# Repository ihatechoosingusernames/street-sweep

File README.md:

# street-sweep
A low cost version of the Ferris Sweep ergonomic keyboard.

Based on a [CH552G](https://raw.githubusercontent.com/WeActStudio/WeActStudio.CH552CoreBoard/master/Datasheet/CH552DS1_en.PDF) chip, this PCB can be completely constructed with all components apart from MX switches by JLCPCB for a total of €27.28 (5x PCBs), making for a per-keyboard cost of €10.91.

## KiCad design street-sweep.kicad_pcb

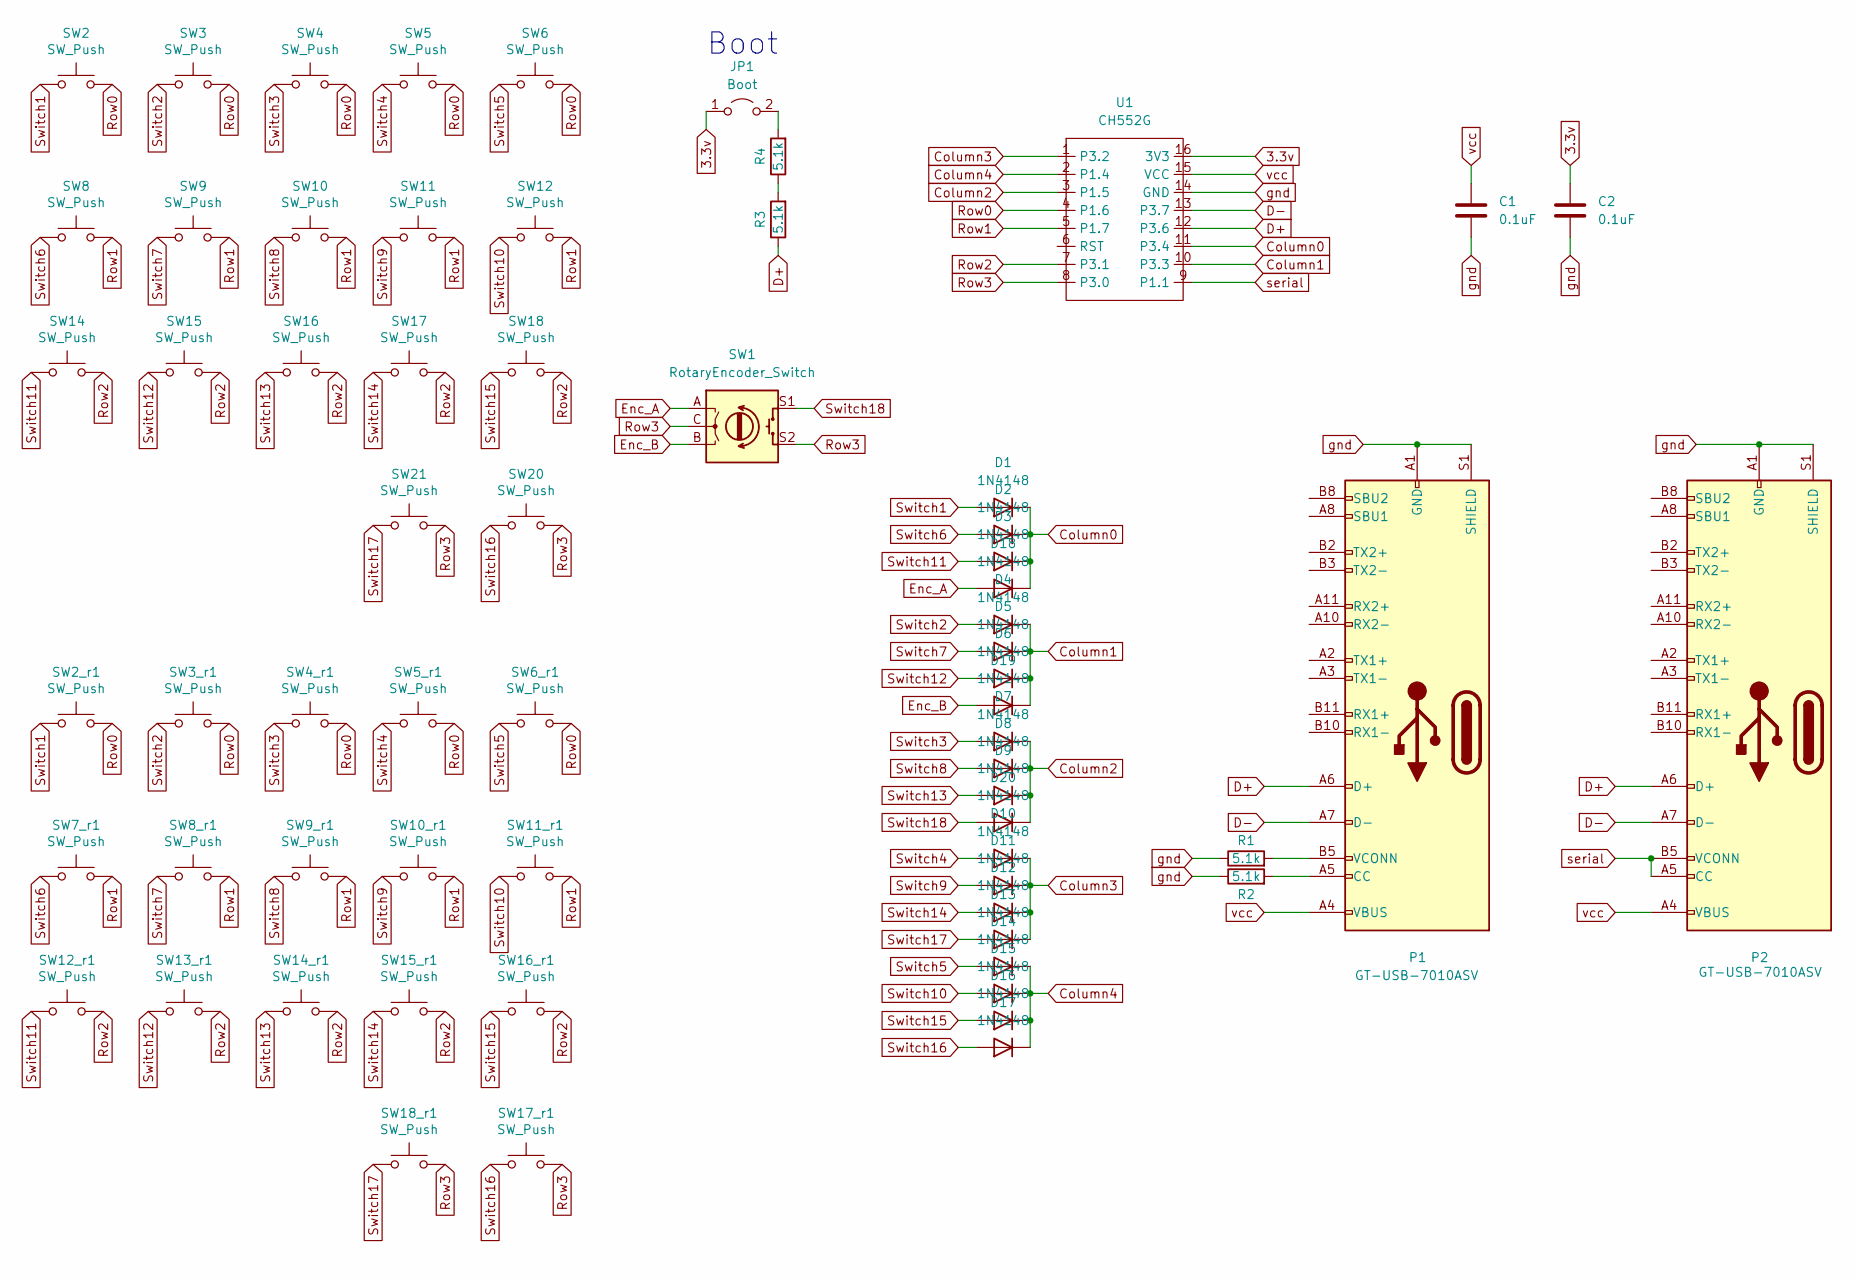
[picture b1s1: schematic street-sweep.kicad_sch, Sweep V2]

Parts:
C1, C2: 0.1uF; C_0805_2012Metric_Pad1.18x1.45mm_HandSolder
D1, D2, D3, D4, D5, D6, D7, D8, D9, D10, D11, D12, D13, D14, D15, D16, D17, D18, D19, D20: 1N4148; D_SOD-123
JP1: Boot; PinHeader_1x02_P2.54mm_Vertical
P1, P2: GT-USB-7010ASV; USB_C_Receptacle_G-Switch_GT-USB-7010ASV
R1, R2, R3, R4: 5.1k; R_0805_2012Metric
SW1: RotaryEncoder_Switch; RotaryEncoder_Alps_EC11E-Switch_Vertical_H20mm
SW2, SW2_r1, SW3, SW3_r1, SW4, SW4_r1, SW5, SW5_r1, SW6, SW6_r1, SW7_r1, SW8, SW8_r1, SW9, SW9_r1, SW10, SW10_r1, SW11, SW11_r1, SW12, SW12_r1, SW13_r1, SW14, SW14_r1, SW15, SW15_r1, SW16, SW16_r1, SW17, SW17_r1, SW18, SW18_r1, SW20, SW21: SW_Push; SW_Cherry_MX_1.00u_PCB
U1: CH552G

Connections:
3.3v: C2.1, JP1.1 (A), U1.16 (3V3)
Column0: D1.1 (K), D2.1 (K), D3.1 (K), D18.1 (K), U1.11 (P3.4)
Column1: D4.1 (K), D5.1 (K), D6.1 (K), D19.1 (K), U1.10 (P3.3)
Column2: D7.1 (K), D8.1 (K), D9.1 (K), D20.1 (K), U1.3 (P1.5)
Column3: D10.1 (K), D11.1 (K), D12.1 (K), D13.1 (K), U1.1 (P3.2)
Column4: D14.1 (K), D15.1 (K), D16.1 (K), D17.1 (K), U1.2 (P1.4)
D+: P1.A6 (D+), P2.A6 (D+), R3.1, U1.12 (P3.6)
D-: P1.A7 (D-), P2.A7 (D-), U1.13 (P3.7)
Enc_A: D18.2 (A), SW1.A
Enc_B: D19.2 (A), SW1.B
unnamed: JP1.2 (B), R4.2
unnamed: P1.A5 (CC), R2.2
unnamed: P1.B5 (VCONN), R1.2
unnamed: R3.2, R4.1
Row0: SW2.2, SW2_r1.2, SW3.2, SW3_r1.2, SW4.2, SW4_r1.2, SW5.2, SW5_r1.2, SW6.2, SW6_r1.2, U1.4 (P1.6)
Row1: SW7_r1.2, SW8.2, SW8_r1.2, SW9.2, SW9_r1.2, SW10.2, SW10_r1.2, SW11.2, SW11_r1.2, SW12.2, U1.5 (P1.7)
Row2: SW12_r1.2, SW13_r1.2, SW14.2, SW14_r1.2, SW15.2, SW15_r1.2, SW16.2, SW16_r1.2, SW17.2, SW18.2, U1.7 (P3.1)
Row3: SW1.C, SW1.S2, SW17_r1.2, SW18_r1.2, SW20.2, SW21.2, U1.8 (P3.0)
Switch1: D1.2 (A), SW2.1, SW2_r1.1
Switch2: D4.2 (A), SW3.1, SW3_r1.1
Switch3: D7.2 (A), SW4.1, SW4_r1.1
Switch4: D10.2 (A), SW5.1, SW5_r1.1
Switch5: D14.2 (A), SW6.1, SW6_r1.1
Switch6: D2.2 (A), SW7_r1.1, SW8.1
Switch7: D5.2 (A), SW8_r1.1, SW9.1
Switch8: D8.2 (A), SW9_r1.1, SW10.1
Switch9: D11.2 (A), SW10_r1.1, SW11.1
Switch10: D15.2 (A), SW11_r1.1, SW12.1
Switch11: D3.2 (A), SW12_r1.1, SW14.1
Switch12: D6.2 (A), SW13_r1.1, SW15.1
Switch13: D9.2 (A), SW14_r1.1, SW16.1
Switch14: D12.2 (A), SW15_r1.1, SW17.1
Switch15: D16.2 (A), SW16_r1.1, SW18.1
Switch16: D17.2 (A), SW17_r1.1, SW20.1
Switch17: D13.2 (A), SW18_r1.1, SW21.1
Switch18: D20.2 (A), SW1.S1
gnd: C1.2, C2.2, P1.A1 (GND), P1.A12 (GND), P1.B1 (GND), P1.B12 (GND), P1.S1 (SHIELD), P2.A1 (GND), P2.A12 (GND), P2.B1 (GND), P2.B12 (GND), P2.S1 (SHIELD), R1.1, R2.1, U1.14 (GND)
serial: P2.A5 (CC), P2.B5 (VCONN), U1.9 (P1.1)
vcc: C1.1, P1.A4 (VBUS), P1.A9 (VBUS), P1.B4 (VBUS), P1.B9 (VBUS), P2.A4 (VBUS), P2.A9 (VBUS), P2.B4 (VBUS), P2.B9 (VBUS), U1.15 (VCC)

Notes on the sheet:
Boot

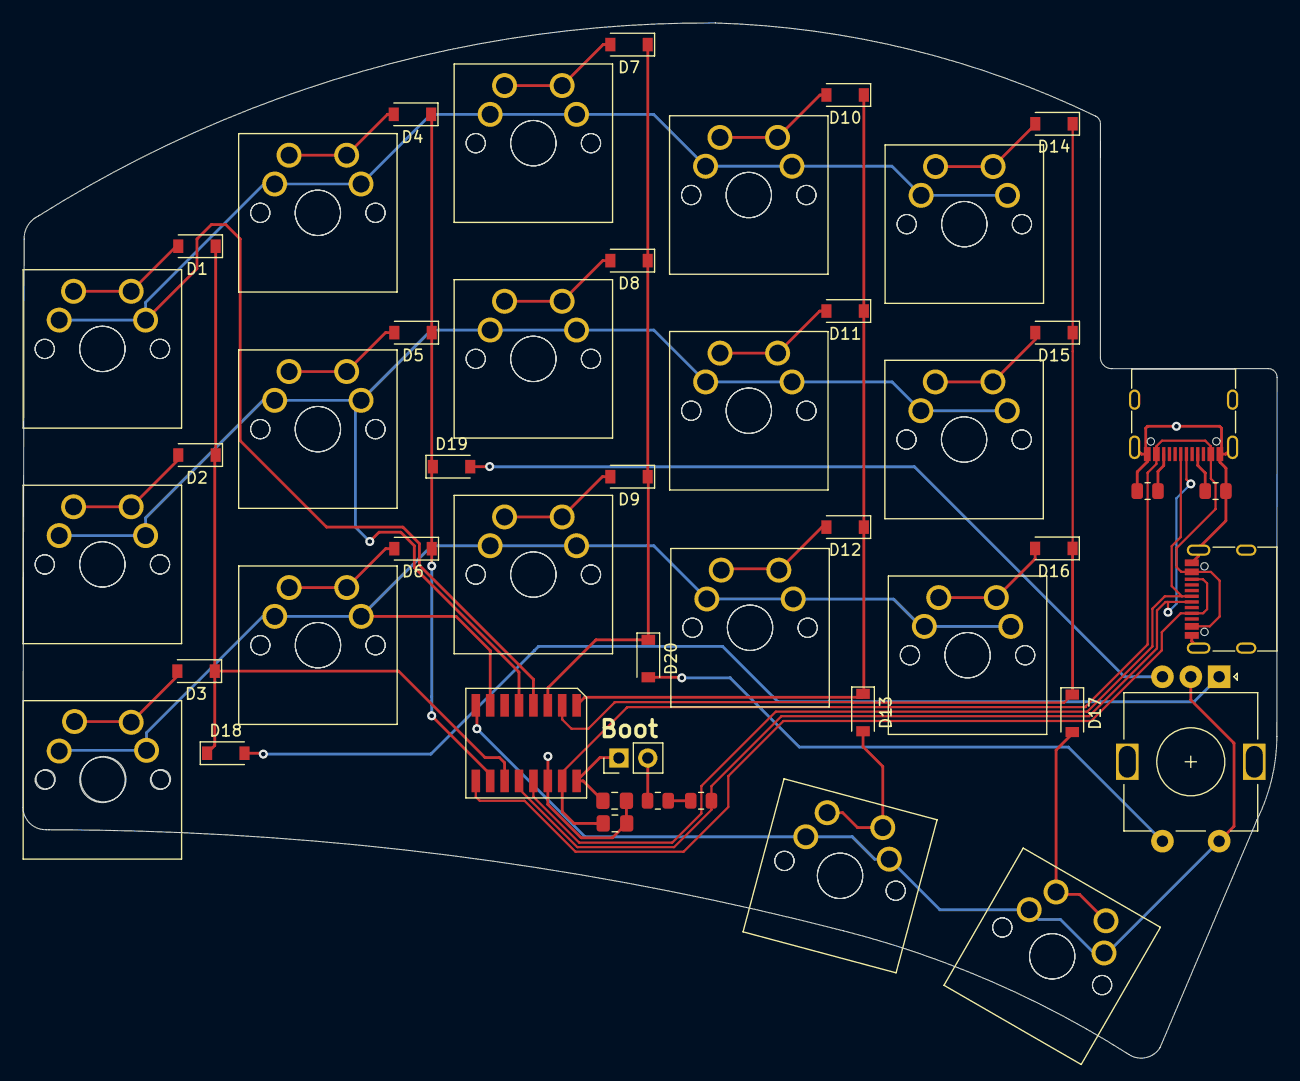
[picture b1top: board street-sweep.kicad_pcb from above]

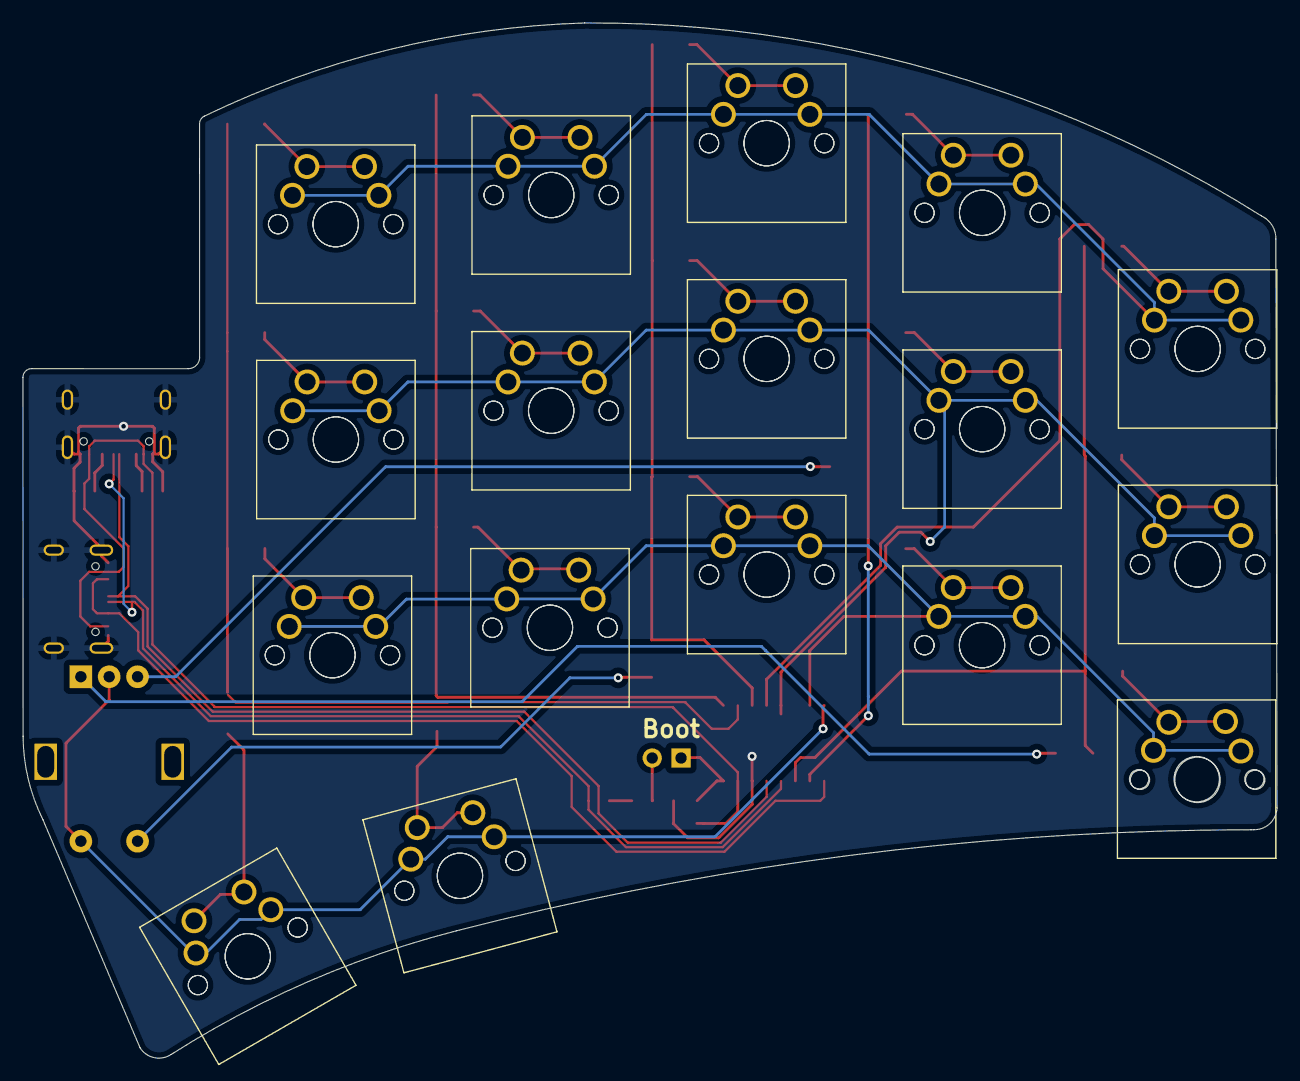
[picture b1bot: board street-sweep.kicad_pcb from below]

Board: 2 copper layers, 110.6 x 91.3 mm, 65 parts (17 on the bottom side), 39 nets.

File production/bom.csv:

Designator,Footprint,Quantity,Value,LCSC Part #
C1,0805,1,0.1uF,
C2,0805,1,0.1uF,
"D1, D10, D11, D12, D13, D14, D15, D16, D17, D18, D19, D2, D20, D3, D4, D5, D6, D7, D8, D9",D_SOD-123,20,1N4148,
JP1,PinHeader_1x02_P2.54mm_Vertical,1,Boot,
"P1, P2",USB_C_Receptacle_G-Switch_GT-USB-7010ASV,2,GT-USB-7010ASV,
R1,0805,1,5.1k,
R2,0805,1,5.1k,
R3,0805,1,5.1k,
R4,0805,1,5.1k,
SW1,RotaryEncoder_Alps_EC11E-Switch_Vertical_H20mm,1,RotaryEncoder_Switch,
"SW10, SW10_r1, SW11, SW11_r1, SW12, SW12_r1, SW13_r1, SW14, SW14_r1, SW15, SW15_r1, SW16, SW16_r1, SW17, SW17_r1, SW18, SW18_r1, SW2, SW20, SW21, SW2_r1, SW3, SW3_r1, SW4, SW4_r1, SW5, SW5_r1, SW6, SW6_r1, SW7_r1, SW8, SW8_r1, SW9, SW9_r1",SW_Cherry_MX_1.00u_PCB,34,SW_Push,
U1,CH552G,1,CH552G,

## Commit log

2023-03-08 Made first pass at converting to an STM32 based design.
2023-03-21 Latest changes on STM32
2023-03-21 Laid out CH552 Board version with two USB-C ports and fixes for flashing.
2023-03-21 Added render image, updated readme.
2023-03-21 Actually added the render this time.
2024-01-17 Rotary Encoder added, still on CH552G
